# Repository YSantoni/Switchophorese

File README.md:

# Switchophorese
An open source Field Inversion Gel Electrophoresis module, programmable via touchscreen.
Connect this module between your classic lab power supply and your gel tray.

This open source laboratory equipment is based on :

- Arduino mega
- Tft 2.8 lcd touch screen shield
- Mosfet full h-bridge circuit

Specs : suitable for gel electrophoresis or field inversion electrophoresis

- 40v to 200v
- max 6.5 amps
- 20ns switching time

Programmable elements :

- pre-heating timer
- runtime timer
- first pulse duration
- last pulse duration
- ratio forward/backward pulse
- linear or exponential time ramp

Libraries used :

https://github.com/prenticedavid/MCUFRIEND_kbv

https://github.com/adafruit/Adafruit_TouchScreen

**First screen** : Welcome screen, touch anywhere to begin.

**Second screen** : Set the duration for the pre-heating timer "Init" and the runtime timer "Run". Select hour, minute, or second and set it with "+" and "-" square, when done touch                 "OK" to go to the next screen.

**Third screen** : Set the duration of the first and last forward pulse of the run (minimum steps of 10ms). Set the duration of the backward pulse as a ratio of the forward pulse.
                You can choose linear or exponential to have the desired evolution of pulse duration during the run.

**Fourth screen** : The recap screen with all the parameters you have entered, when ready press "Begin".

**Fifth screen** : The run screen

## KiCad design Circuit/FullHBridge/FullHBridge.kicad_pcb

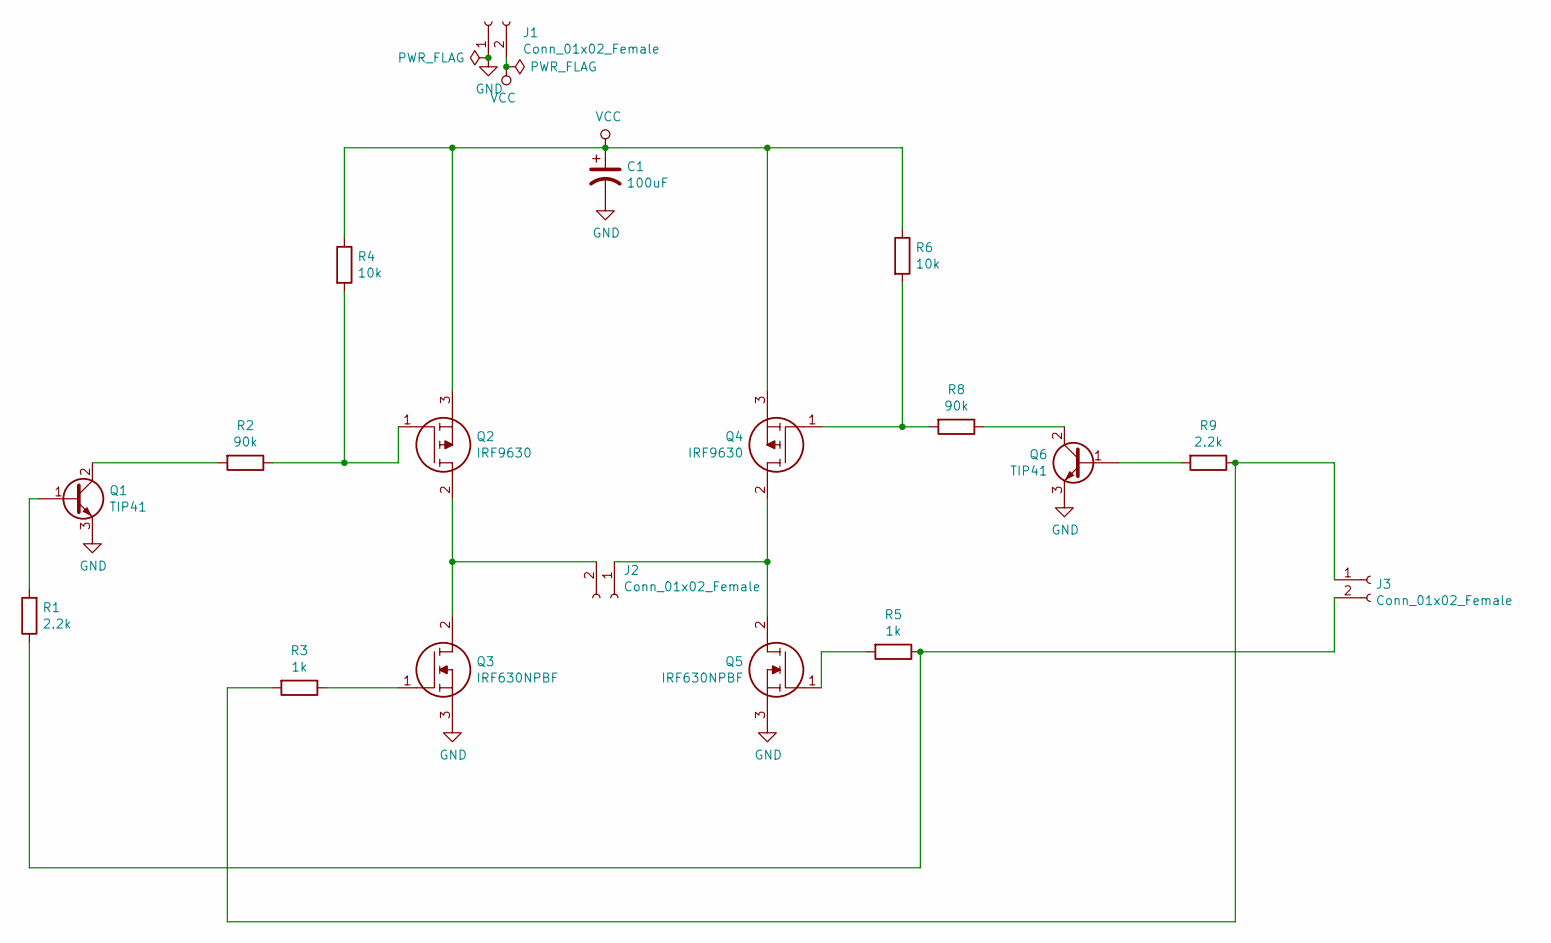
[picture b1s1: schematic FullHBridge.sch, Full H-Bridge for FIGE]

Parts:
C1: 100uF; CP_Radial_D16.0mm_P7.50mm
J1, J2, J3: Conn_01x02_Female; JST_NV_B02P-NV_1x02_P5.00mm_Vertical
Q1, Q6: TIP41; TO-220-3_Vertical
Q2, Q4: IRF9630; TO254P465X1024X2050-3P; Manufacturer_Part_Number IRF9630; Mouser Part Number 844-IRF9630
Q3, Q5: IRF630NPBF; TO254P469X1042X1967-3P; Manufacturer_Part_Number IRF630NPBF; Mouser Part Number 942-IRF630NPBF
R1, R9: 2.2k; R_Axial_DIN0204_L3.6mm_D1.6mm_P7.62mm_Horizontal
R2, R8: 90k; R_Axial_DIN0204_L3.6mm_D1.6mm_P7.62mm_Horizontal
R3, R5: 1k; R_Axial_DIN0204_L3.6mm_D1.6mm_P7.62mm_Horizontal
R4, R6: 10k; R_Axial_DIN0204_L3.6mm_D1.6mm_P7.62mm_Horizontal

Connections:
GND: C1.2, J1.1, Q1.3 (E), Q3.3, Q5.3, Q6.3 (E)
unnamed: J2.1, Q4.2, Q5.2
unnamed: J2.2, Q2.2, Q3.2
unnamed: J3.1, R3.2, R9.1
unnamed: J3.2, R1.1, R5.1
unnamed: Q1.1 (B), R1.2
unnamed: Q1.2 (C), R2.2
unnamed: Q2.1, R2.1, R4.2
unnamed: Q3.1, R3.1
unnamed: Q4.1, R6.2, R8.2
unnamed: Q5.1, R5.2
unnamed: Q6.1 (B), R9.2
unnamed: Q6.2 (C), R8.1
VCC: C1.1, J1.2, Q2.3, Q4.3, R4.1, R6.1

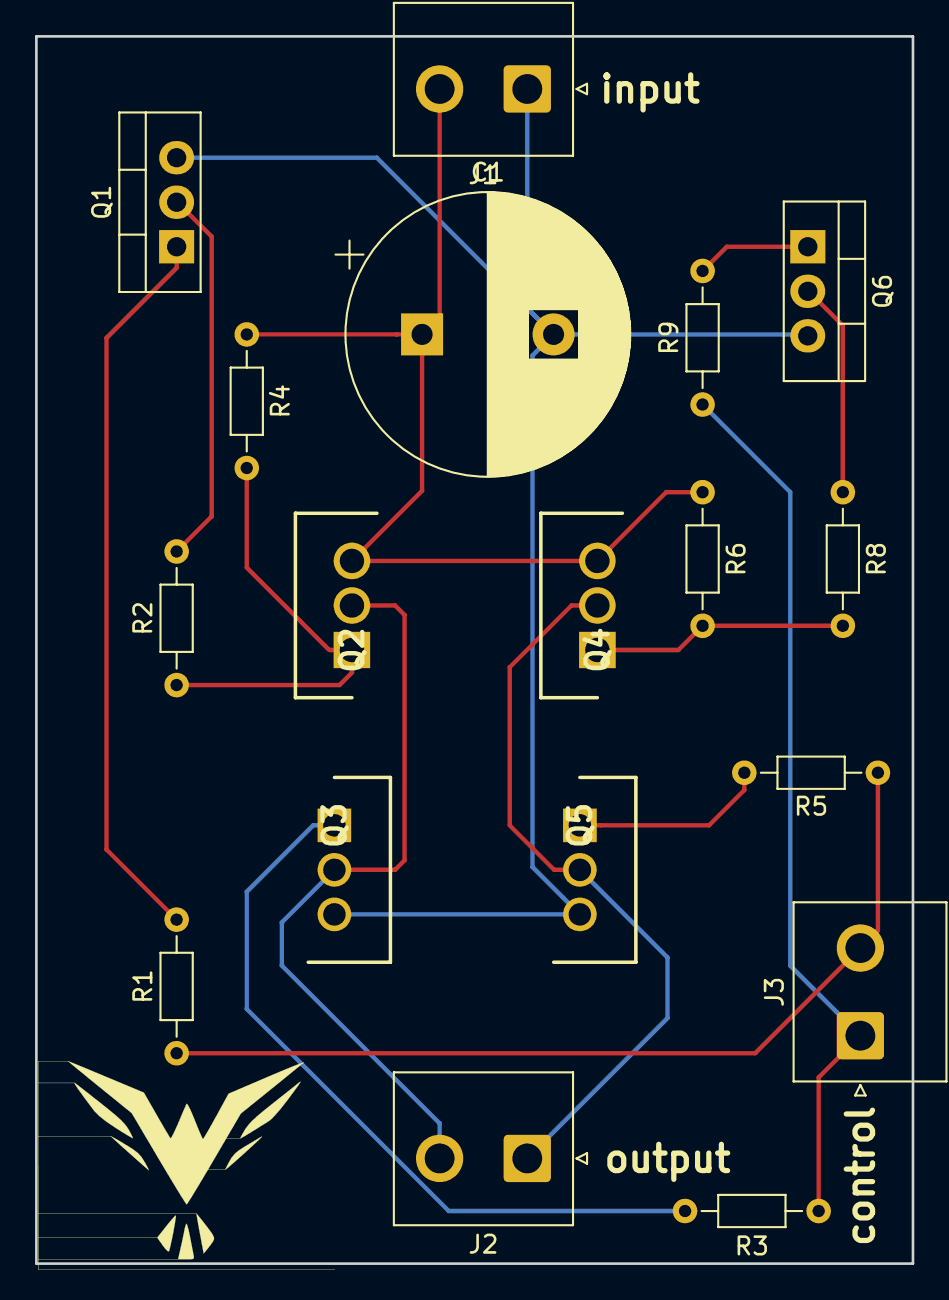
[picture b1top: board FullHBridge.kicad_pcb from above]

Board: 2 copper layers, 50.0 x 70.0 mm, 18 parts (0 on the bottom side), 14 nets.

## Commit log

2021-05-19 Update README.md
    description of the project added
2021-05-19 Update README.md
    added clarity
2021-05-19 Update README.md
    added photo
2021-05-19 Create Code
2021-05-19 Create Switchophorese
2021-05-19 Create Kicad
2021-05-20 Update README.md
    added screen pictures
2021-05-20 Create 3D printing
2021-05-20 Add files via upload
    Prices and retailers remain to be added
